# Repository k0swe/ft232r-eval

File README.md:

Evaluation board for the FTDI FT232R USB to serial chip.

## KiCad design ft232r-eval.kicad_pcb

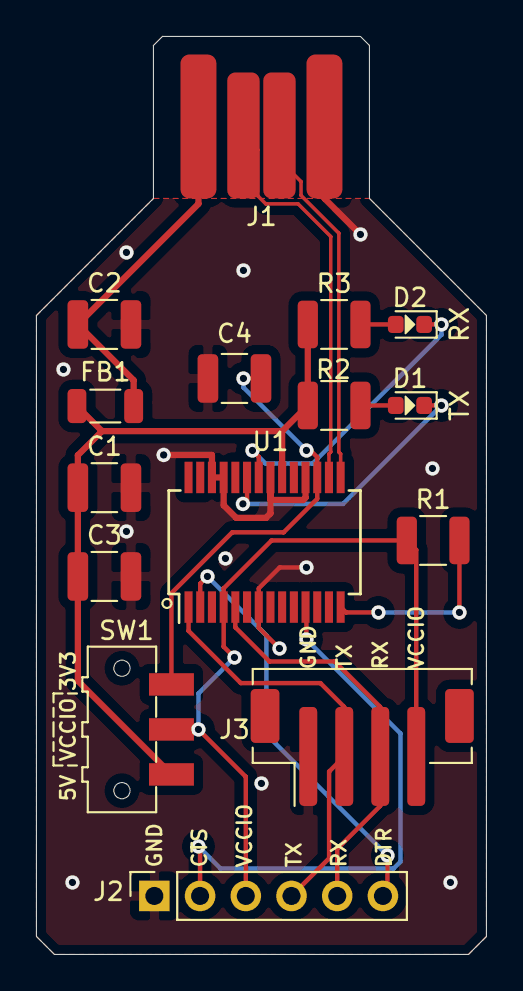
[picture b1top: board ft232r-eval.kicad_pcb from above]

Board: 2 copper layers, 25.0 x 51.0 mm, 16 parts (1 on the bottom side), 16 nets.

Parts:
C1, C4: 100nF; C_1210_3225Metric
C2: 10nF; C_1210_3225Metric
C3: 4.7μF; C_1210_3225Metric
D1: TX; LED_0603_1608Metric
D2: RX; LED_0603_1608Metric
FB1: Ferrite_Bead; L_1206_3216Metric
J1: USB_A; USB-A_trace
J2: FTDI; PinSocket_1x06_P2.54mm_Vertical
J3: JST; JST_PH_B4B-PH-SM4-TB_1x04-1MP_P2.00mm_Vertical
LOGO1: Logo_Open_Hardware_Small; OSHW-Logo2_9.8x8mm_SilkScreen
R1: 10kΩ; R_1210_3225Metric
R2, R3: 270Ω; R_1210_3225Metric
SW1: VIO_SEL; SW_SPDT_CK-JS102011SAQN
U1: FT232RL; SSOP-28_5.3x10.2mm_P0.65mm

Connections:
+3V3: C4.1, SW1.1, U1.17
/CTS: J2.2, U1.11
/D+: J1.3, U1.15
/D-: J1.2, U1.16
/DTR: J2.6, U1.2
/PWREN: R1.2, U1.14
/RXD: J2.5, J3.3, U1.5
/RXLED: D2.1, U1.22
/TXD: J2.4, J3.2, U1.1
/TXLED: D1.1, U1.23
/VIO: J2.3, J3.4, R1.1, SW1.2, U1.4
GND: C1.2, C2.2, C3.2, C4.2, J1.4, J2.1, J3.1, U1.7, U1.18, U1.21, U1.25, U1.26
unnamed: D1.2, R2.1
unnamed: D2.2, R3.2
VBUS: C2.1, FB1.2, J1.1
VCC: C1.1, C3.1, FB1.1, R2.2, R3.1, SW1.3, U1.20

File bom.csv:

Refs,value,Vendor,Vendor Part #,Price,datasheet,footprint
C1,100nF,Mouser,80-C1210C104K5RAUTO,0.37,https://www.mouser.com/datasheet/2/212/KEM_C1023_X7R_AUTO_SM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,Capacitor_SMD:C_1210_3225Metric
C2,10nF,Mouser,77-VJ1210Y103KXBAT,0.14,https://www.mouser.com/datasheet/2/427/vjcommercialseries-17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,Capacitor_SMD:C_1210_3225Metric
C3,4.7μF,Mouser,963-EMK325B7475MN-T,0.35,https://www.mouser.com/datasheet/2/396/mlcc02_e-1307760.pdf,Capacitor_SMD:C_1210_3225Metric
C4,100nF,Mouser,80-C1210C104K5RAUTO,0.37,https://www.mouser.com/datasheet/2/212/KEM_C1023_X7R_AUTO_SM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,Capacitor_SMD:C_1210_3225Metric
D1,TX,Mouser,710-150060RS75000,0.15,https://www.mouser.com/datasheet/2/445/150060RS75000-1715052.pdf,LED_SMD:LED_0603_1608Metric
D2,RX,Mouser,710-150060RS75000,0.15,https://www.mouser.com/datasheet/2/445/150060RS75000-1715052.pdf,LED_SMD:LED_0603_1608Metric
FB1,Ferrite_Bead,Mouser,81-BLM31PG121SN1L,0.3,https://www.mouser.com/datasheet/2/281/ENFA0006-1915741.pdf,Inductor_SMD:L_1206_3216Metric
J1,USB_A,-,-,0,-,usb-a:USB-A_trace
J2,FTDI,Mouser,517-974-01-06-RK,0.8,https://www.mouser.com/datasheet/2/1/ts0815-31700.pdf,Connector_PinSocket_2.54mm:PinSocket_1x06_P2.54mm_Vertical
J3,JST,Mouser,485-4392,0.35,https://www.mouser.com/datasheet/2/737/4389_C13924-001_CCP-W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,Connector_JST:JST_PH_B4B-PH-SM4-TB_1x04-1MP_P2.00mm_Vertical
R1,10kΩ,Mouser,660-RK73B2ETTD103J,0.14,https://www.mouser.com/datasheet/2/219/RK73B-1825463.pdf,Resistor_SMD:R_1210_3225Metric
R2,270Ω,Mouser,660-RK73B2ETTD271J,0.14,https://www.mouser.com/datasheet/2/219/RK73B-1825463.pdf,Resistor_SMD:R_1210_3225Metric
R3,270Ω,Mouser,660-RK73B2ETTD271J,0.14,https://www.mouser.com/datasheet/2/219/RK73B-1825463.pdf,Resistor_SMD:R_1210_3225Metric
SW1,VIO_SEL,Mouser,611-JS102011SAQN,0.51,https://www.mouser.com/datasheet/2/60/js-1841892.pdf,Button_Switch_SMD:SW_SPDT_CK-JS102011SAQN
U1,FT232RL,Mouser,895-FT232RL,4.6,https://www.ftdichip.com/Support/Documents/DataSheets/ICs/DS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,Package_SO:SSOP-28_5.3x10.2mm_P0.65mm

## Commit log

2021-03-24 Fix FTDI header footprint
2021-04-01 Fix JST part number
    Adafruit 4392 is horizontal, not vertical.
2021-04-03 Add labels for J2 and J3 pins
2021-04-04 Convert BOM from one per line to grouped
2021-04-05 Thicker traces and fix 3D render
2021-04-07 Add LED directional arrows
2021-04-14 Clean up libraries
2021-04-15 License under CC BY 4.0
2021-04-19 Small updates
2021-04-19 Change BOM from grouped to one line per component
2021-04-24 Add OSHW logo

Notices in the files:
ft232r-eval.kicad_pcb:
Licensed under Creative Commons CC-BY-4.0
